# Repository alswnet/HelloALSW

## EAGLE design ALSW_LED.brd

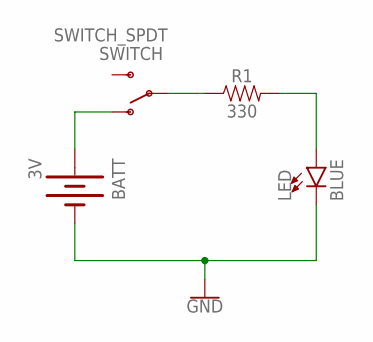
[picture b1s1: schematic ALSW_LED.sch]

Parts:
BATT: 3V; BATTCON_24.5MM
LED: BLUE; LED-1206
R1: 330; 0603
SWITCH: SWITCH_SPDT; KPS-1290

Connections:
GND: BATT.2 (-), LED.C
unnamed: BATT.1 (+), SWITCH.O
unnamed: R1.1, SWITCH.P
unnamed: LED.A, R1.2

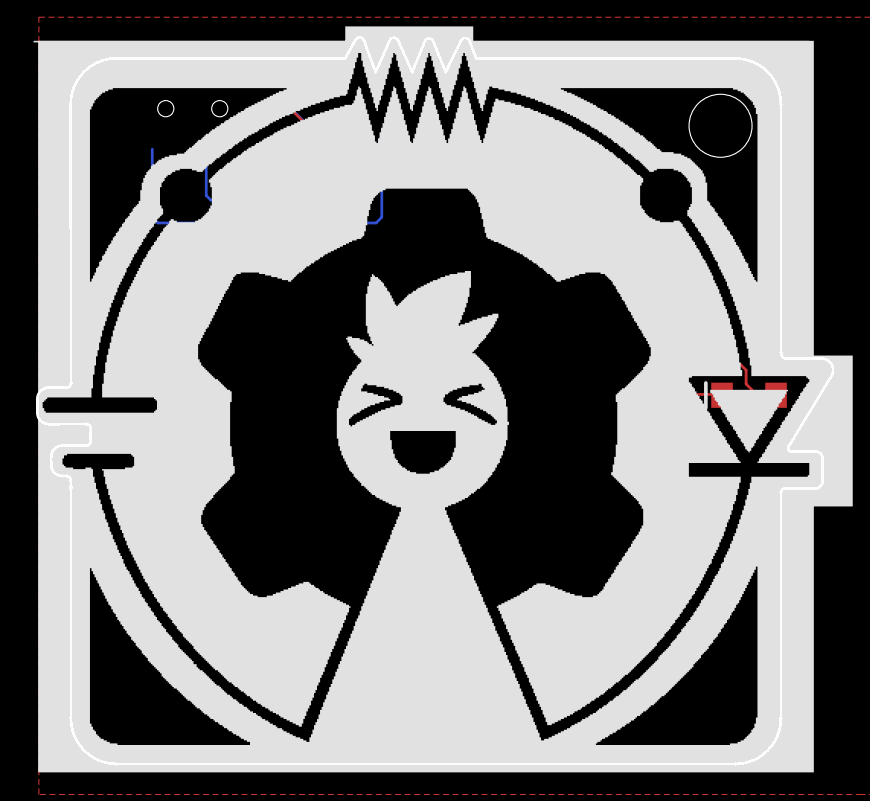
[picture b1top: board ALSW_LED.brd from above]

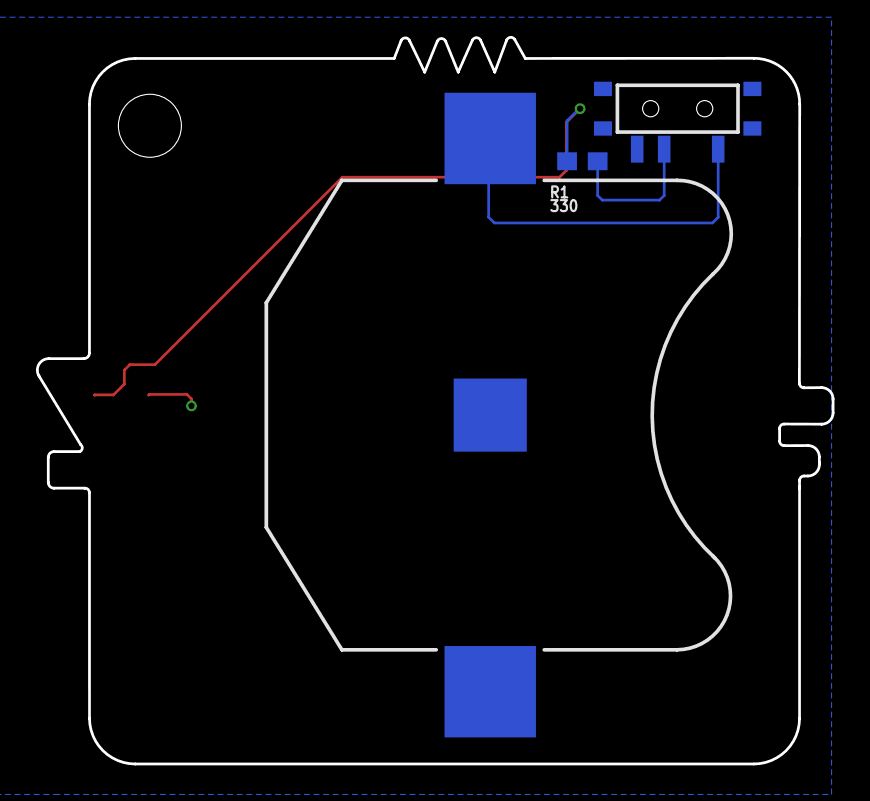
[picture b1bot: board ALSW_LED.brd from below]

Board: 2 copper layers, 44.2 x 40.4 mm, 4 parts (3 on the bottom side), 4 nets.

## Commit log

2018-09-06 Proyecto de Hola mundo con imageotipo de ALSW

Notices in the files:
parts and their libraries:
SparkFun-Retired: Licensing: Creative Commons ShareAlike 4.0 International - https://creativecommons.org/licenses/by-sa/4.0
